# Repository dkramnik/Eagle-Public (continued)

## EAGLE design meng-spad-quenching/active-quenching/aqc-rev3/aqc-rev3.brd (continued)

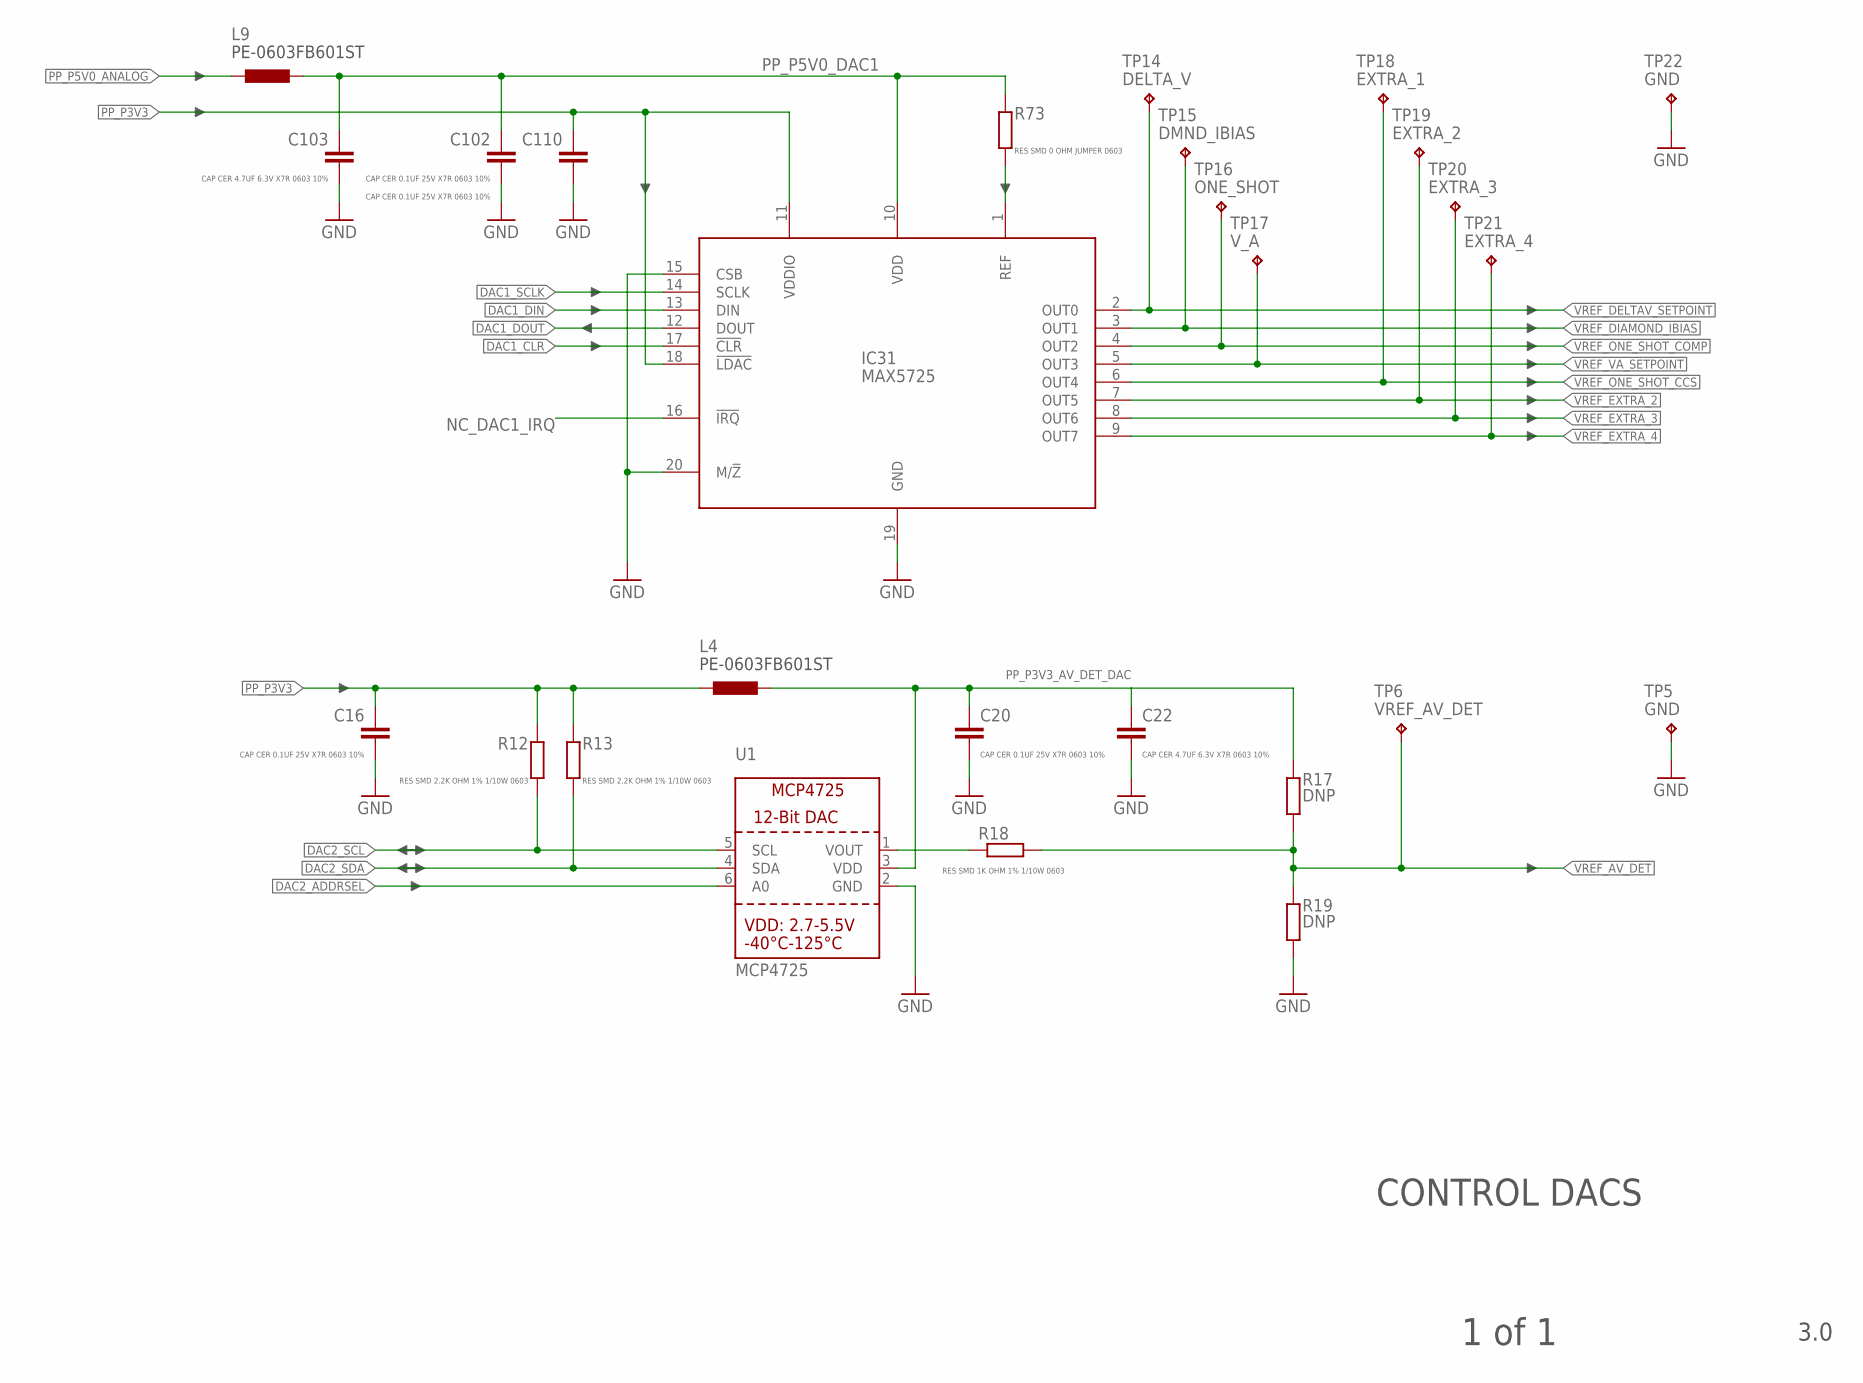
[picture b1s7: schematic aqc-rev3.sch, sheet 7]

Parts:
C16, C20, C102, C110: CAP CER 0.1UF 25V X7R 0603 10%; C0603
C22, C103: CAP CER 4.7UF 6.3V X7R 0603 10%; C0603
IC31: MAX5725; TSSOP20
L4, L9: PE-0603FB601ST; R0603
R12, R13: RES SMD 2.2K OHM 1% 1/10W 0603; R0603
R17, R19: DNP; R0603
R18: RES SMD 1K OHM 1% 1/10W 0603; R0603
R73: RES SMD 0 OHM JUMPER 0603; R0603
TP5, TP22: GND; KEYSTONE_5000_MINIATURE
TP6: VREF_AV_DET; KEYSTONE_5000_MINIATURE
TP14: DELTA_V; KEYSTONE_5000_MINIATURE
TP15: DMND_IBIAS; KEYSTONE_5000_MINIATURE
TP16: ONE_SHOT; KEYSTONE_5000_MINIATURE
TP17: V_A; KEYSTONE_5000_MINIATURE
TP18: EXTRA_1; KEYSTONE_5000_MINIATURE
TP19: EXTRA_2; KEYSTONE_5000_MINIATURE
TP20: EXTRA_3; KEYSTONE_5000_MINIATURE
TP21: EXTRA_4; KEYSTONE_5000_MINIATURE
U1: MCP4725; SOT23-6

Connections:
DAC1_!CLR: IC31.17 (!CLR); also elsewhere on the board
DAC1_DIN: IC31.13 (DIN); also elsewhere on the board
DAC1_DOUT: IC31.12 (DOUT); also elsewhere on the board
DAC1_SCLK: IC31.14 (SCLK); also elsewhere on the board
DAC2_ADDRSEL: U1.6 (A0); also elsewhere on the board
DAC2_SCL: R12.2, U1.5 (SCL); also elsewhere on the board
DAC2_SDA: R13.2, U1.4 (SDA); also elsewhere on the board
GND: C16.2, C20.2, C22.2, C102.2, C103.2, C110.2, IC31.15 (CSB), IC31.19 (GND), IC31.20 (M/!Z), R19.1, TP5.P$1, TP22.P$1, U1.2 (GND); also elsewhere on the board
unnamed: R18.2, U1.1 (VOUT)
unnamed: IC31.1 (REF), R73.2
NC_DAC1_IRQ: IC31.16 (!IRQ)
PP_P3V3: C16.1, C110.1, IC31.11 (VDDIO), IC31.18 (!LDAC), L4.1, R12.1, R13.1; also elsewhere on the board
PP_P3V3_AV_DET_DAC: C20.1, C22.1, L4.2, R17.2, U1.3 (VDD)
PP_P5V0_ANALOG: L9.1; also elsewhere on the board
PP_P5V0_DAC1: C102.1, C103.1, IC31.10 (VDD), L9.2, R73.1
VREF_AV_DET: R17.1, R18.1, R19.2, TP6.P$1; also elsewhere on the board
VREF_DELTAV_SETPOINT: IC31.2 (OUT0), TP14.P$1; also elsewhere on the board
VREF_DIAMOND_IBIAS: IC31.3 (OUT1), TP15.P$1; also elsewhere on the board
VREF_EXTRA_2: IC31.7 (OUT5), TP19.P$1
VREF_EXTRA_3: IC31.8 (OUT6), TP20.P$1
VREF_EXTRA_4: IC31.9 (OUT7), TP21.P$1
VREF_ONE_SHOT_CCS: IC31.6 (OUT4), TP18.P$1; also elsewhere on the board
VREF_ONE_SHOT_COMP: IC31.4 (OUT2), TP16.P$1; also elsewhere on the board
VREF_VA_SETPOINT: IC31.5 (OUT3), TP17.P$1; also elsewhere on the board

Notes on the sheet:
CONTROL DACS
3.0
1 of 1

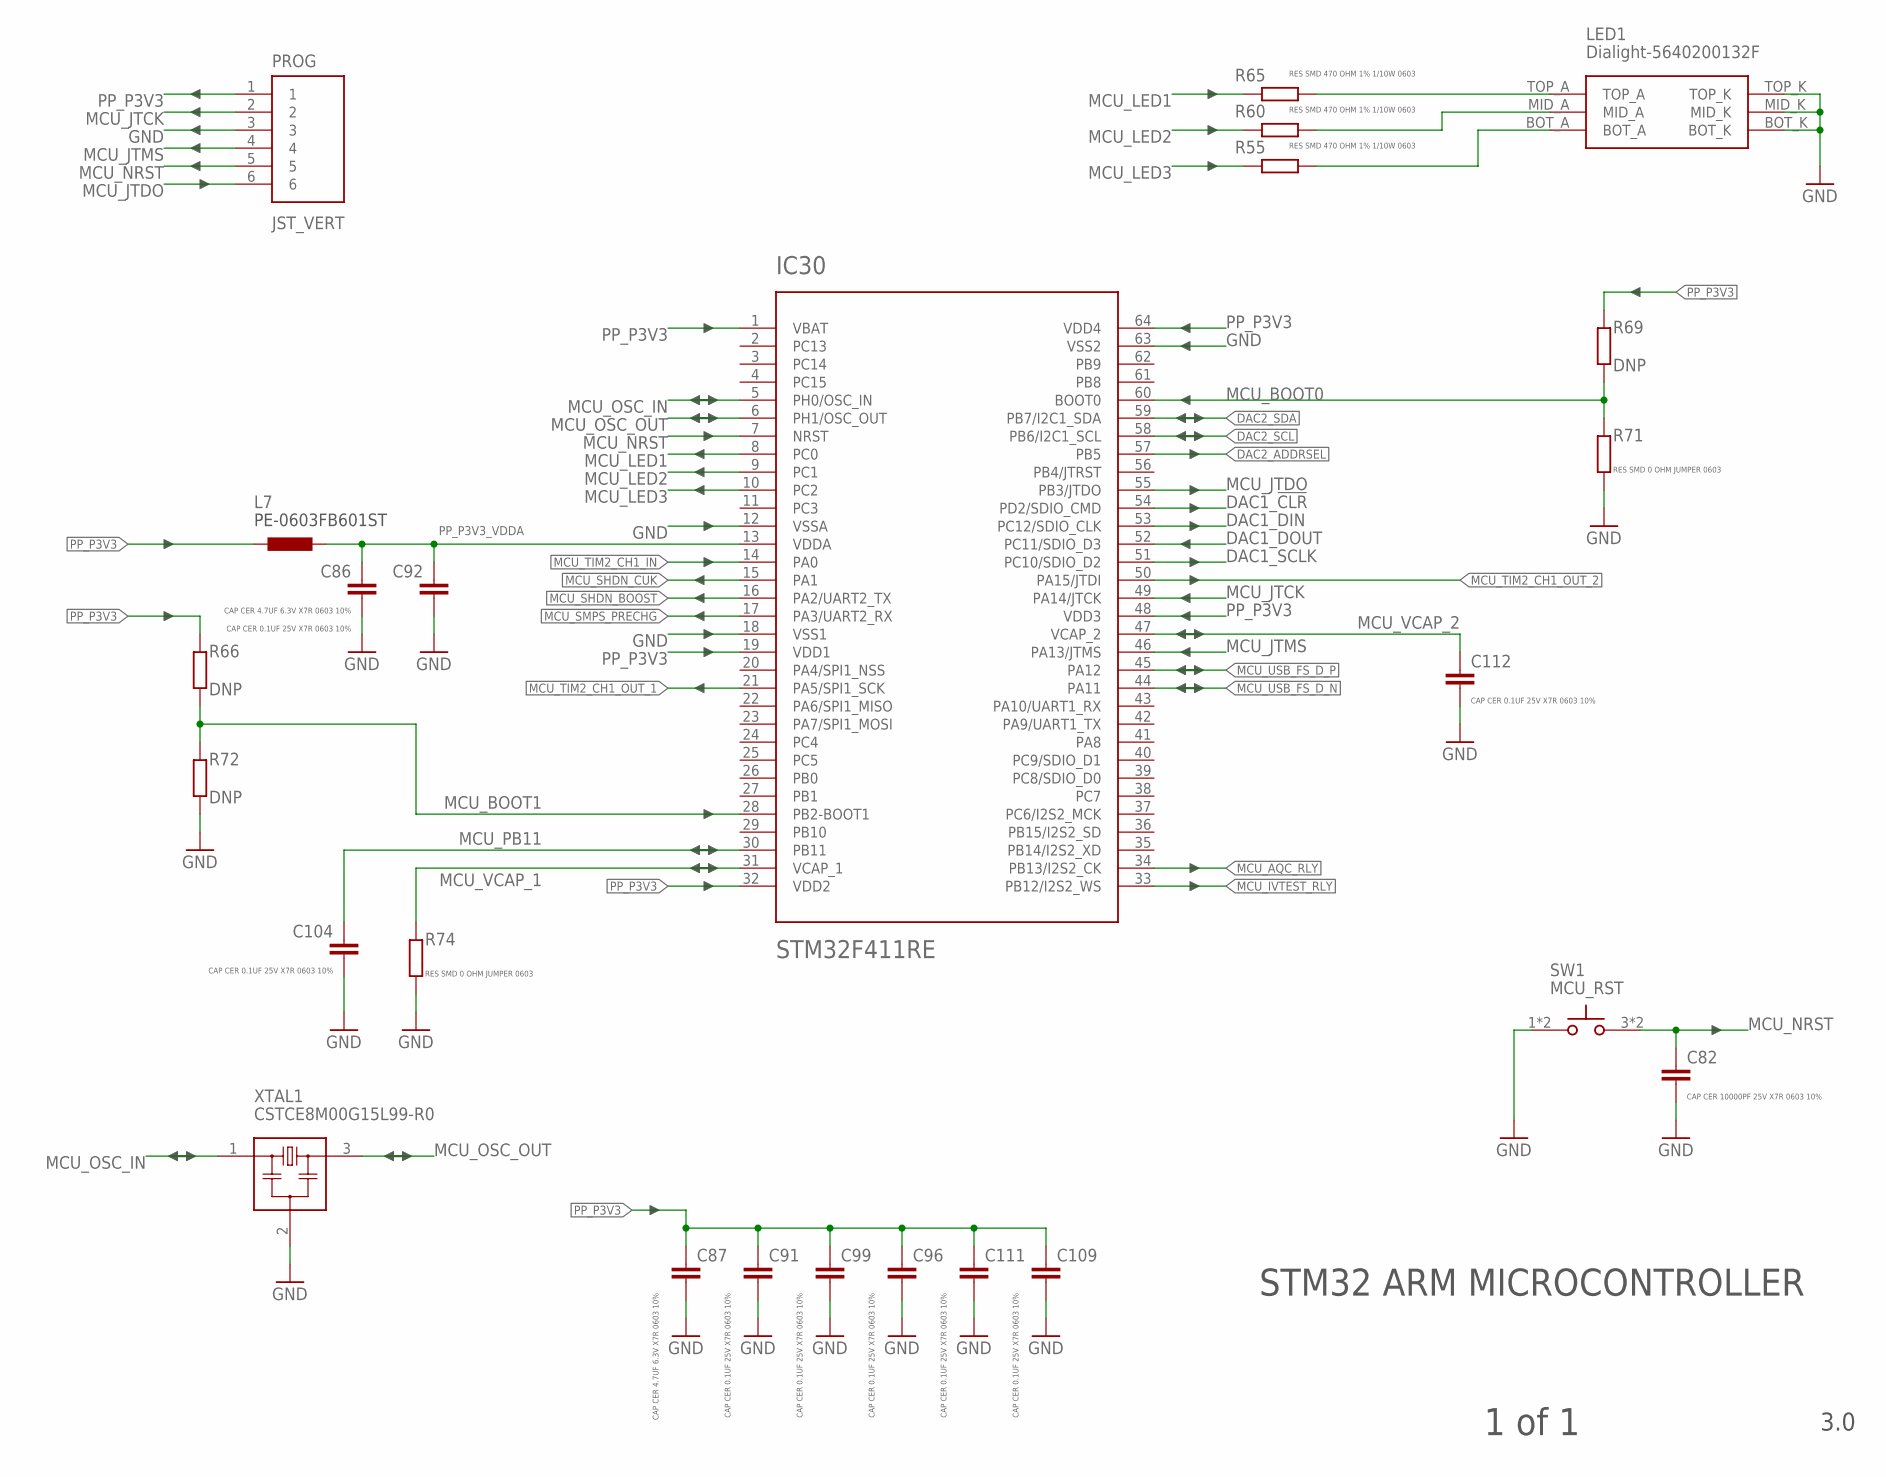
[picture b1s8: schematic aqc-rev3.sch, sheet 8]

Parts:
C82: CAP CER 10000PF 25V X7R 0603 10%; C0603
C86, C87: CAP CER 4.7UF 6.3V X7R 0603 10%; C0603
C91, C92, C96, C99, C104, C109, C111, C112: CAP CER 0.1UF 25V X7R 0603 10%; C0603
IC30: STM32F411RE; TQFP64_STM32
L7: PE-0603FB601ST; R0603
LED1: Dialight-5640200132F; CBI-564-0X00-XXX
PROG: JST_VERT; JST-6-SMD-VERT-1.0MM
R55, R60, R65: RES SMD 470 OHM 1% 1/10W 0603; R0603
R66, R69, R72: DNP; R0603
R71, R74: RES SMD 0 OHM JUMPER 0603; R0603
SW1: MCU_RST; E-SWITCH-TL3305AF160QG
XTAL1: CSTCE8M00G15L99-R0; CSTCE_G15L/CSTCE_GH5L

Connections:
!MCU_SHDN_BOOST: IC30.16 (PA2/UART2_TX); also elsewhere on the board
!MCU_SHDN_CUK: IC30.15 (PA1); also elsewhere on the board
!MCU_SMPS_PRECHG: IC30.17 (PA3/UART2_RX); also elsewhere on the board
DAC1_!CLR: IC30.54 (PD2/SDIO_CMD); also elsewhere on the board
DAC1_DIN: IC30.53 (PC12/SDIO_CLK); also elsewhere on the board
DAC1_DOUT: IC30.52 (PC11/SDIO_D3); also elsewhere on the board
DAC1_SCLK: IC30.51 (PC10/SDIO_D2); also elsewhere on the board
DAC2_ADDRSEL: IC30.57 (PB5); also elsewhere on the board
DAC2_SCL: IC30.58 (PB6/I2C1_SCL); also elsewhere on the board
DAC2_SDA: IC30.59 (PB7/I2C1_SDA); also elsewhere on the board
GND: C82.2, C86.2, C87.2, C91.2, C92.2, C96.2, C99.2, C104.2, C109.2, C111.2, C112.2, IC30.12 (VSSA), IC30.18 (VSS1), IC30.63 (VSS2), LED1.BOT_K, LED1.MID_K, LED1.TOP_K, PROG.3, R71.2, R72.2, R74.2, SW1.1, SW1.2, XTAL1.2 (GND); also elsewhere on the board
MCU_AQC_RLY: IC30.34 (PB13/I2S2_CK); also elsewhere on the board
MCU_BOOT0: IC30.60 (BOOT0), R69.2, R71.1
MCU_BOOT1: IC30.28 (PB2-BOOT1), R66.2, R72.1
MCU_IVTEST_RLY: IC30.33 (PB12/I2S2_WS); also elsewhere on the board
MCU_JTCK: IC30.49 (PA14/JTCK), PROG.2
MCU_JTDO: IC30.55 (PB3/JTDO), PROG.6
MCU_JTMS: IC30.46 (PA13/JTMS), PROG.4
MCU_LED1: IC30.8 (PC0), R65.2
MCU_LED2: IC30.9 (PC1), R60.2
MCU_LED3: IC30.10 (PC2), R55.2
MCU_NRST: C82.1, IC30.7 (NRST), PROG.5, SW1.3, SW1.4
MCU_OSC_IN: IC30.5 (PH0/OSC_IN), XTAL1.1 (LEFT)
MCU_OSC_OUT: IC30.6 (PH1/OSC_OUT), XTAL1.3 (RIGHT)
MCU_PB11: C104.1, IC30.30 (PB11)
MCU_TIM2_CH1_IN: IC30.14 (PA0); also elsewhere on the board
MCU_TIM2_CH1_OUT_1: IC30.21 (PA5/SPI1_SCK); also elsewhere on the board
MCU_TIM2_CH1_OUT_2: IC30.50 (PA15/JTDI); also elsewhere on the board
MCU_USB_FS_D_N: IC30.44 (PA11); also elsewhere on the board
MCU_USB_FS_D_P: IC30.45 (PA12); also elsewhere on the board
MCU_VCAP_1: IC30.31 (VCAP_1), R74.1
MCU_VCAP_2: C112.1, IC30.47 (VCAP_2)
unnamed: LED1.TOP_A, R65.1
unnamed: LED1.MID_A, R60.1
unnamed: LED1.BOT_A, R55.1
PP_P3V3: C87.1, C91.1, C96.1, C99.1, C109.1, C111.1, IC30.1 (VBAT), IC30.19 (VDD1), IC30.32 (VDD2), IC30.48 (VDD3), IC30.64 (VDD4), L7.1, PROG.1, R66.1, R69.1; also elsewhere on the board
PP_P3V3_VDDA: C86.1, C92.1, IC30.13 (VDDA), L7.2

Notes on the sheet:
STM32 ARM MICROCONTROLLER
3.0
1 of 1

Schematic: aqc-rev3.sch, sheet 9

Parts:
C26: CAP ALUM POLY 47UF 20% 20V SMD; CT7343
C79, C106, C107: CAP CER 0.1UF 25V X7R 0603 10%; C0603
C95: CAP CER 0.1UF 10V X7R 0402 10%; C0402
C97: CAP CER 10000PF 10V X7R 0402 10%; C0402
C98, C101: CAP CER 47PF 16V C0G 0402 5%; C0402
C105: CAP CER 10000PF 25V X7R 0603 10%; C0603
C108: CAP CER 4.7UF 6.3V X7R 0603 10%; C0603
H1, H2, H3, H4: MOUNT-PAD-ROUND3.2; 3,2-PAD
IC29: USBLC6-2SC6Y; SOT23-6L
IC32: LM1117; SOT-223
L8, L10: MI0805J102R-10; R0805
Q1: DMG2305UX-13; SOT23-WIDE
R58: RES SMD 4.7K OHM 1% 1/10W 0603; R0603
R62: RES SMD 100K OHM 1% 1/10W 0603; R0603
R67, R70: RES SMD 22 OHM 1% 1/10W 0402; R0402
TP23: TPTP15R; TP15R
X3, X6: KEYSTONE-7774
X8: 61729-0010BLF; PN61729-S

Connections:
!MCU_SMPS_PRECHG: R58.2; also elsewhere on the board
GND: C26.-, C95.2, C97.2, C98.2, C101.2, C105.2, C106.2, C107.2, C108.2, H1.B3,2, H2.B3,2, H3.B3,2, H4.B3,2, IC29.2 (GND), IC32.1 (GND), L10.2, X3.1, X3.2, X3.3, X3.4, X6.1, X6.2, X6.3, X6.4, X8.S1, X8.S2; also elsewhere on the board
MCU_USB_FS_D_N: C101.1, R70.1; also elsewhere on the board
MCU_USB_FS_D_P: C98.1, R67.1; also elsewhere on the board
unnamed: C79.1, Q1.1 (G), R58.1, R62.1
PP_P3V3: C95.1, C97.1, C106.1, IC29.5 (VBUS), IC32.2 (OUT), IC32.4 (TAB), TP23.TP; also elsewhere on the board
SMPS_USB_VDD: C26.+, C79.2, Q1.3 (D); also elsewhere on the board
USBCONN_P1: C105.1, L8.1, X8.1
USBCONN_P4: L10.1, X8.4
USBD_CONN_N: IC29.3 (I/O2), X8.2
USBD_CONN_P: IC29.1 (I/O1_1), X8.3
USBD_TVS_N: IC29.4 (I/O2_2), R70.2
USBD_TVS_P: IC29.6 (I/O1_2), R67.2
USB_VDD: C107.1, C108.1, IC32.3 (IN), L8.2, Q1.2 (S), R62.2

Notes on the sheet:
USB INPUT AND INRUSH LIMITING
3.0
1 of 1

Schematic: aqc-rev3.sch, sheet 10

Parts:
C3: CAP CER 1000PF 50V X7R 0603 10%; C0603
C4: CAP CER 1300PF 50V C0G 0603 5%; C0603
C13, C14, C25: CAP ALUM POLY 47UF 20% 20V SMD; CT7343
C15: CAP CER 4.7UF 25V X7R 0805 10%; C0805
C17: CAP CER 0.1UF 25V X7R 0603 10%; C0603
C18: CAP CER 0.015UF 50V X7R 0603 10%; C0603
C19: CAP CER 220PF 50V C0G 0603 5%; C0603
D1: CDBA140SL-HF; DO214AC
IC3: LT1534-1; SO16
L1: 25n; R0603
L2: Wurth-7447709471; WE_INDUCTOR_SIZE_CODE_1210
L3: SRF0703-820M; SRF0703
R3: RES SMD 0 OHM JUMPER 0603; R0603
R4, R9: DNP; R0603
R5: RES SMD 29.4K OHM 1% 1/10W 0603; R0603
R6: RES SMD 2.49K OHM 1% 1/10W 0603; R0603
R7: RES SMD 10 OHM 1% 1/10W 0603; R0603
R8: RES SMD 16.9K OHM 1% 1/10W 0603; R0603
R14, R15: RES SMD 1K OHM 1% 1/10W 0603; R0603
R16: RES SMD 6.8K OHM 1% 1/10W 0603; R0603
TP2, TP7: TPB1,27; B1,27

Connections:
!MCU_SHDN_BOOST: IC3.12 (!SHDN); also elsewhere on the board
BOOST_STAGE1: C13.+, C14.+, D1.C, L3.1, R4.1, R9.1
BOOST_SW_NODE: D1.A, IC3.2 (COL), L2.2, R7.1
GND: C3.1, C4.2, C13.-, C14.-, C15.2, C17.2, C18.2, C19.2, C25.-, IC3.1 (GND), IC3.8 (GND), IC3.9 (GND), IC3.16 (GND), L1.2, R6.2, R8.1, R14.2, R15.2; also elsewhere on the board
LBOOST_2: L3.2, L3.3
unnamed: IC3.7 (FB), R5.1, R6.1
unnamed: IC3.3 (PGND), L1.1
unnamed: C4.1, IC3.5 (CT)
unnamed: IC3.13 (RCSL), R15.1
unnamed: IC3.14 (RVSL), R14.1
unnamed: C3.2, R7.2
unnamed: C18.1, R16.1
unnamed: C19.1, IC3.11 (VC), R16.2
unnamed: IC3.6 (RT), R8.2
unnamed: R3.2, R4.2, R5.2
PP_P16V0_BOOST: C25.+, L3.4, R3.1, R9.2; also elsewhere on the board
SMPS_USB_VDD: C15.1, C17.1, IC3.15 (VIN), L2.1; also elsewhere on the board
TP_NFB_BOOST: IC3.10 (NFB), TP7.TP
TP_SYNC_BOOST: IC3.4 (SYNC), TP2.TP

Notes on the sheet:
POSITIVE DC/DC SMPS
3.0
1 of 1

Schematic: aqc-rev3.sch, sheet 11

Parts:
C27: CAP CER 10UF 10V X7R 1206 10%; C1206
C31: CAP CER 10000PF 25V X7R 0603 10%; C0603
C32: CAP CER 1300PF 50V C0G 0603 5%; C0603
C42: CAP ALUM POLY 68UF 20% 16V SMD; CT7343
C45, C57: CAP CER 4.7UF 25V X7R 0805 10%; C0805
C56: CAP CER 10UF 16V X7R 0805 20%; C0805
C67: CAP CER 0.1UF 25V X7R 0603 10%; C0603
C68: CAP CER 0.033UF 50V X7R 0603 10%; C0603
C69, C71: DNP; C0603
D2: CDBA140SL-HF; DO214AC
IC10: LT1534-1; SO16
L5: 25n; R0603
L6: SRF0703-820M; SRF0703
R29: RES SMD 100 OHM 1% 1/8W 0603; R0603
R30: RES SMD 16.9K OHM 1% 1/10W 0603; R0603
R41: RES SMD 1.4K OHM 1% 1/10W 0603; R0603
R43, R44, R48: RES SMD 1K OHM 1% 1/10W 0603; R0603
R45: RES SMD 2K OHM 1% 1/10W 0603; R0603
TP8, TP10: TPB1,27; B1,27

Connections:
!MCU_SHDN_CUK: IC10.12 (!SHDN); also elsewhere on the board
GND: C27.2, C31.2, C32.2, C45.2, C56.2, C57.2, C67.2, C68.2, C69.2, C71.2, D2.C, IC10.1 (GND), IC10.8 (GND), IC10.9 (GND), IC10.16 (GND), L5.2, R30.1, R43.2, R44.2, R48.2; also elsewhere on the board
unnamed: C32.1, IC10.5 (CT)
unnamed: IC10.3 (PGND), L5.1
unnamed: IC10.13 (RCSL), R44.1
unnamed: IC10.14 (RVSL), R43.1
unnamed: C31.1, R29.2
unnamed: C68.1, R45.1
unnamed: C69.1, IC10.11 (VC), R45.2
unnamed: IC10.6 (RT), R30.2
unnamed: IC10.10 (NFB), R41.2, R48.1
unnamed: C42.+, IC10.2 (COL), L6.3, R29.1
unnamed: C42.-, C71.1, D2.A, L6.4
PP_N6V0_CUK: C56.1, L6.2, R41.1; also elsewhere on the board
SMPS_USB_VDD: C27.1, C45.1, C57.1, C67.1, IC10.15 (VIN), L6.1; also elsewhere on the board
TP_FB_CUK: IC10.7 (FB), TP10.TP
TP_SYNC_CUK: IC10.4 (SYNC), TP8.TP

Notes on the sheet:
NEGATIVE DC/DC SMPS
3.0
1 of 1

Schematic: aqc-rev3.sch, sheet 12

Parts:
C1, C2, C5, C6, C41, C54: CAP CER 10000PF 25V X7R 0603 10%; C0603
C7, C8, C9, C10, C46, C53: CAP CER 0.1UF 25V X7R 0603 10%; C0603
C11: CAP CER 10UF 25V X5R 0805 10%; C0805
C12, C39: CAP CER 10UF 16V X7R 0805 20%; C0805
IC1, IC2: TPS7A4901; MSOP-8_POWER_PAD
IC9: TPS7A3001; MSOP-8_POWER_PAD
R1, R34: RES SMD 24K OHM 1% 1/10W 0603; R0603
R2: RES SMD 11.8K OHM 1% 1/10W 0603; R0603
R10, R32: RES SMD 76.8K OHM 1% 1/10W 0603; R0603
R11: RES SMD 137K OHM 1% 1/10W 0603; R0603
TP1, TP3, TP4, TP11: TPTP15R; TP15R

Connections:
GND: C1.2, C2.2, C7.2, C8.2, C9.2, C10.2, C11.2, C12.2, C39.2, C46.2, C53.2, C54.2, IC1.4 (GND), IC1.PAD (GND), IC2.4 (GND), IC2.PAD (GND), IC9.4 (GND), IC9.PAD (GND), R1.2, R2.2, R34.2, TP4.TP; also elsewhere on the board
LDO_N10V0_FB_CH1: C41.2, IC9.2 (FB), R32.1, R34.1
LDO_N10V0_NR_SS_CH1: C54.1, IC9.6 (NR/SS)
LDO_P5V0_FB_CH1: C5.2, IC1.2 (FB), R1.1, R10.1
LDO_P5V0_NR_SS_CH1: C1.1, IC1.6 (NR/SS)
LDO_P10V0_FB_CH1: C6.2, IC2.2 (FB), R2.1, R11.1
LDO_P10V0_NR_SS_CH1: C2.1, IC2.6 (NR/SS)
PP_N5V0_ANALOG: C39.1, C41.1, C46.1, IC9.1 (OUT), R32.2, TP11.TP; also elsewhere on the board
PP_N6V0_CUK: C53.1, IC9.5 (EN), IC9.8 (IN); also elsewhere on the board
PP_P5V0_ANALOG: C5.1, C9.1, C12.1, IC1.1 (OUT), R10.2, TP3.TP; also elsewhere on the board
PP_P15V0_ANALOG: C6.1, C7.1, C10.1, C11.1, IC1.5 (EN), IC1.8 (IN), IC2.1 (OUT), R11.2, TP1.TP; also elsewhere on the board
PP_P16V0_BOOST: C8.1, IC2.5 (EN), IC2.8 (IN); also elsewhere on the board

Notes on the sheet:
LINEAR POSTREGULATORS
3.0
1 of 1

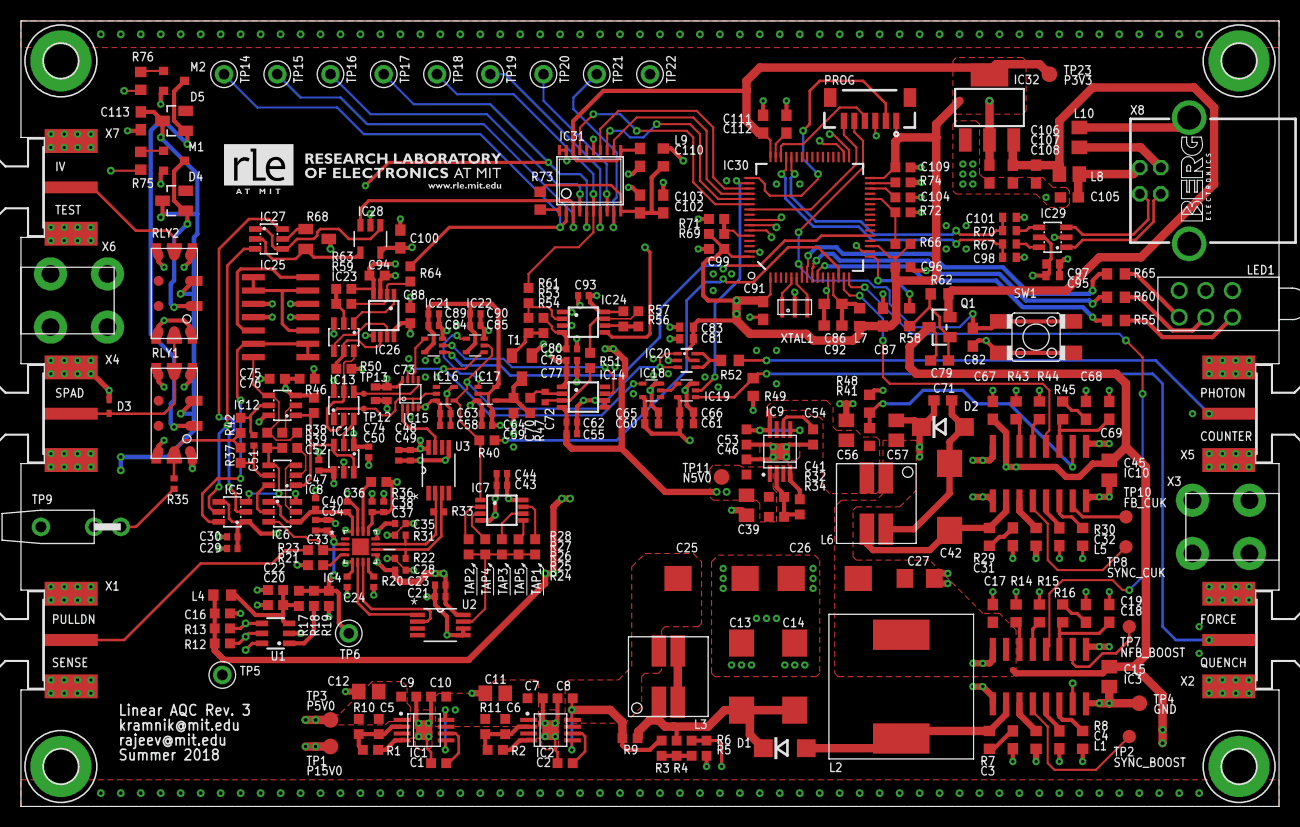
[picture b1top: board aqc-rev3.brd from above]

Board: 4 copper layers, 120.0 x 74.9 mm, 285 parts (0 on the bottom side), 166 nets.

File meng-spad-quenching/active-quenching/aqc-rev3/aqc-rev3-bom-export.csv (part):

"Qty";"Value";"Device";"Package";"Parts";"Description";"MF";"MPN";"OC_FARNELL";"OC_NEWARK";"PACKAGE";"PROD_ID";"SUPPLIER";"TP_SIGNAL_NAME";"VALUE";
"6";"0R";"R-EU_R0603";"R0603";"R3, R47, R51, R71, R73, R74";"RESISTOR, European symbol";"";"";"";"";"";"";"";"";"";
"1";"100R";"R-EU_R0402";"R0402";"R33";"RESISTOR, European symbol";"";"";"";"";"";"";"";"";"";
"3";"100R";"R-EU_R0603";"R0603";"R29, R75, R76";"RESISTOR, European symbol";"";"";"";"";"";"";"";"";"";
"2";"100R, 1%";"R-EU_R0603";"R0603";"R37, R42";"RESISTOR, European symbol";"";"";"";"";"";"";"";"";"";
"3";"100k";"R-EU_R0603";"R0603";"R56, R57, R62";"RESISTOR, European symbol";"";"";"";"";"";"";"";"";"";
"21";"100n";"C-EUC0402";"C0402";"C23, C29, C33, C35, C36, C37, C43, C49, C55, C58, C59, C61, C65, C73, C77, C80, C83, C89, C90, C93, C95";"CAPACITOR, European symbol";"";"";"";"";"";"";"";"";"";
"28";"100n";"C-EUC0603";"C0603";"C7, C8, C9, C10, C16, C17, C20, C46, C53, C67, C76, C79, C88, C91, C92, C94, C96, C99, C100, C102, C104, C106, C107, C109, C110, C111, C112, C113";"CAPACITOR, European symbol";"";"";"";"";"";"";"";"";"";
"1";"100p";"C-EUC0402";"C0402";"C51";"CAPACITOR, European symbol";"";"";"";"";"";"";"";"";"";
"1";"100p";"C-EUC0603";"C0603";"C70";"CAPACITOR, European symbol";"";"";"";"";"";"";"";"";"";
"1";"102k, 1%";"R-EU_R0603";"R0603";"R64";"RESISTOR, European symbol";"";"";"";"";"";"";"";"";"";
"1";"10R";"R-EU_R0603";"R0603";"R7";"RESISTOR, European symbol";"";"";"";"";"";"";"";"";"";
"2";"10k";"R-EU_R0603";"R0603";"R36, R54";"RESISTOR, European symbol";"";"";"";"";"";"";"";"";"";
"22";"10n";"C-EUC0402";"C0402";"C21, C24, C28, C30, C34, C38, C40, C44, C47, C48, C50, C60, C62, C63, C64, C66, C74, C78, C81, C84, C85, C97";"CAPACITOR, European symbol";"";"";"";"";"";"";"";"";"";
"11";"10n";"C-EUC0603";"C0603";"C1, C2, C5, C6, C31, C41, C52, C54, C75, C82, C105";"CAPACITOR, European symbol";"";"";"";"";"";"";"";"";"";
"3";"10u";"C-EUC0805";"C0805";"C11, C12, C39";"CAPACITOR, European symbol";"";"";"";"";"";"";"";"";"";
"1";"10u";"C-EUC1206";"C1206";"C27";"CAPACITOR, European symbol";"";"";"";"";"";"";"";"";"";
"1";"10u, 10V";"C-EUC0805";"C0805";"C56";"CAPACITOR, European symbol";"";"";"";"";"";"";"";"";"";
"1";"110R, 1%";"R-EU_R0603";"R0603";"R50";"RESISTOR, European symbol";"";"";"";"";"";"";"";"";"";
"1";"11k8";"R-EU_R0603";"R0603";"R2";"RESISTOR, European symbol";"";"";"";"";"";"";"";"";"";
"1";"127k, 1%";"R-EU_R0603";"R0603";"R59";"RESISTOR, European symbol";"";"";"";"";"";"";"";"";"";
"2";"1300p";"C-EUC0603";"C0603";"C4, C32";"CAPACITOR, European symbol";"";"";"";"";"";"";"";"";"";
"1";"137k";"R-EU_R0603";"R0603";"R11";"RESISTOR, European symbol";"";"";"";"";"";"";"";"";"";
"2";"150R";"R-EU_R0402";"R0402";"R22, R31";"RESISTOR, European symbol";"";"";"";"";"";"";"";"";"";
"1";"15n";"C-EUC0603";"C0603";"C18";"CAPACITOR, European symbol";"";"";"";"";"";"";"";"";"";
"2";"16k9";"R-EU_R0603";"R0603";"R8, R30";"RESISTOR, European symbol";"";"";"";"";"";"";"";"";"";
"6";"1k";"R-EU_R0603";"R0603";"R14, R15, R18, R43, R44, R48";"RESISTOR, European symbol";"";"";"";"";"";"";"";"";"";
"1";"1k4";"R-EU_R0603";"R0603";"R41";"RESISTOR, European symbol";"";"";"";"";"";"";"";"";"";
"1";"1n";"C-EUC0603";"C0603";"C3";"CAPACITOR, European symbol";"";"";"";"";"";"";"";"";"";
"2";"200R, 1%";"R-EU_R0603";"R0603";"R38, R39";"RESISTOR, European symbol";"";"";"";"";"";"";"";"";"";
"2";"220R, 1%";"R-EU_R0603";"R0603";"R23, R46";"RESISTOR, European symbol";"";"";"";"";"";"";"";"";"";
"2";"220k";"R-EU_R0603";"R0603";"R53, R61";"RESISTOR, European symbol";"";"";"";"";"";"";"";"";"";
"1";"220p";"C-EUC0603";"C0603";"C19";"CAPACITOR, European symbol";"";"";"";"";"";"";"";"";"";
"2";"22R";"R-EU_R0402";"R0402";"R67, R70";"RESISTOR, European symbol";"";"";"";"";"";"";"";"";"";
"2";"24k";"R-EU_R0603";"R0603";"R1, R34";"RESISTOR, European symbol";"";"";"";"";"";"";"";"";"";
"2";"25n";"INDUCTOR0603";"R0603";"L1, L5";"";"";"";"";"";"";"";"";"";"";
"1";"274R, 1%";"R-EU_R0603";"R0603";"R63";"RESISTOR, European symbol";"";"";"";"";"";"";"";"";"";
"1";"29k4";"R-EU_R0603";"R0603";"R5";"RESISTOR, European symbol";"";"";"";"";"";"";"";"";"";
"1";"2k";"R-EU_R0603";"R0603";"R45";"RESISTOR, European symbol";"";"";"";"";"";"";"";"";"";
"2";"2k2";"R-EU_R0603";"R0603";"R12, R13";"RESISTOR, European symbol";"";"";"";"";"";"";"";"";"";
"1";"2k49";"R-EU_R0603";"R0603";"R6";"RESISTOR, European symbol";"";"";"";"";"";"";"";"";"";
"1";"33n";"C-EUC0603";"C0603";"C68";"CAPACITOR, European symbol";"";"";"";"";"";"";"";"";"";
"3";"470R";"R-EU_R0603";"R0603";"R55, R60, R65";"RESISTOR, European symbol";"";"";"";"";"";"";"";"";"";
"2";"47p";"C-EUC0402";"C0402";"C98, C101";"CAPACITOR, European symbol";"";"";"";"";"";"";"";"";"";
"4";"47u, 20V";"CPOL-EUCT7343";"CT7343";"C13, C14, C25, C26";"POLARIZED CAPACITOR, European symbol";"";"";"";"";"";"";"";"";"";
"2";"49R9";"R-EU_R0402";"R0402";"R20, R35";"RESISTOR, European symbol";"";"";"";"";"";"";"";"";"";
"3";"49R9";"R-EU_R0603";"R0603";"R40, R49, R52";"RESISTOR, European symbol";"";"";"";"";"";"";"";"";"";
"1";"4k7";"R-EU_R0603";"R0603";"R58";"RESISTOR, European symbol";"";"";"";"";"";"";"";"";"";
"5";"4u7";"C-EUC0603";"C0603";"C22, C86, C87, C103, C108";"CAPACITOR, European symbol";"";"";"";"";"";"";"";"";"";
"3";"4u7";"C-EUC0805";"C0805";"C15, C45, C57";"CAPACITOR, European symbol";"";"";"";"";"";"";"";"";"";
"1";"5640200132F";"CBI-564-0X00-XXX-3LED";"CBI-564-0X00-XXX";"LED1";"";"";"";"";"";"";"";"";"";"564-0x00-xxx";
"1";"68u, 16V";"CPOL-EUCT7343";"CT7343";"C42";"POLARIZED CAPACITOR, European symbol";"";"";"";"";"";"";"";"";"";
"1";"6k8";"R-EU_R0603";"R0603";"R16";"RESISTOR, European symbol";"";"";"";"";"";"";"";"";"";
"1";"732-1699-2-ND";"WE_INDUCTOR";"WE_INDUCTOR_SIZE_CODE_1210";"L2";"";"";"";"";"";"";"";"";"";"";
"1";"74AHC1G04DCK";"74AHC1G04DCK";"SC70-5";"IC18";"INVERTER Gate";"";"";"";"";"";"";"";"";"";
"2";"74AHC1G08DCK";"74AHC1G08DCK";"SC70-5";"IC21, IC22";"2-input AND gate";"";"";"";"";"";"";"";"";"";
"1";"74AHC1G14DCK";"74AHC1G14DCK";"SC70-5";"IC16";"Single Schmitt-Trigger Inverter Gate";"";"";"";"";"";"";"";"";"";
"1";"74AHC1G32DCK";"74AHC1G32DCK";"SC70-5";"IC19";"2-input OR gate";"";"";"";"";"";"";"";"";"";
"2";"76k8";"R-EU_R0603";"R0603";"R10, R32";"RESISTOR, European symbol";"";"";"";"";"";"";"";"";"";
"1";"ADCMP582";"ADCMP582";"QFN50P300X300X80-16N";"IC4";"Ultrafast SiGe Voltage Comparator w/. PECL Outputs";"";"";"";"";"";"";"";"";"";
"2";"BAS40";"BAS40";"SOT23";"D4, D5";"Silicon Schottky Diodes";"";"";"";"";"";"";"";"";"";
"2";"BSS806N";"BSS806N";"SOT23R_INFINEON";"M1, M2";"";"";"";"";"";"";"";"";"";"";
"2";"CDBA140SL-HF";"DIODE-DO214AC";"DO214AC";"D1, D2";"DIODE";"";"";"";"";"";"";"";"";"";
"1";"CONN_FORCE_QUENCH";"SMA-142-0701-881/886";"J502-ND-142-0701-881/886";"X2";"SMA 50 Ohm End Launch Jack Receptacle - Round Contact";"JOHNSON COMPONENTS";"142-0711-871";"unknown";"01C1639";"";"";"";"";"";
"1";"CONN_PHOTON_COUNTER";"SMA-142-0701-881/886";"J502-ND-142-0701-881/886";"X5";"SMA 50 Ohm End Launch Jack Receptacle - Round Contact";"JOHNSON COMPONENTS";"142-0701-881";"1608603";"08B906";"";"";"";"";"";
"1";"CONN_PULLDN_SENSE";"SMA-142-0701-881/886";"J502-ND-142-0701-881/886";"X1";"SMA 50 Ohm End Launch Jack Receptacle - Round Contact";"JOHNSON COMPONENTS";"142-0711-871";"unknown";"01C1639";"";"";"";"";"";
"1";"CONN_SMU";"SMA-142-0701-881/886";"J502-ND-142-0701-881/886";"X7";"SMA 50 Ohm End Launch Jack Receptacle - Round Contact";"JOHNSON COMPONENTS";"142-0701-881";"1608603";"08B906";"";"";"";"";"";
"1";"CONN_SPAD";"SMA-142-0701-881/886";"J502-ND-142-0701-881/886";"X4";"SMA 50 Ohm End Launch Jack Receptacle - Round Contact";"JOHNSON COMPONENTS";"142-0701-881";"1608603";"08B906";"";"";"";"";"";
"2";"CRF05-1A";"MEDER_CRF05-1A";"MEDER_RELAY_CRF";"RLY1, RLY2";"MEDER CRF05-1A RF Reed Relay in a ceramic surface mount package.";"";"";"";"";"";"";"";"";"CRF05-1A";
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
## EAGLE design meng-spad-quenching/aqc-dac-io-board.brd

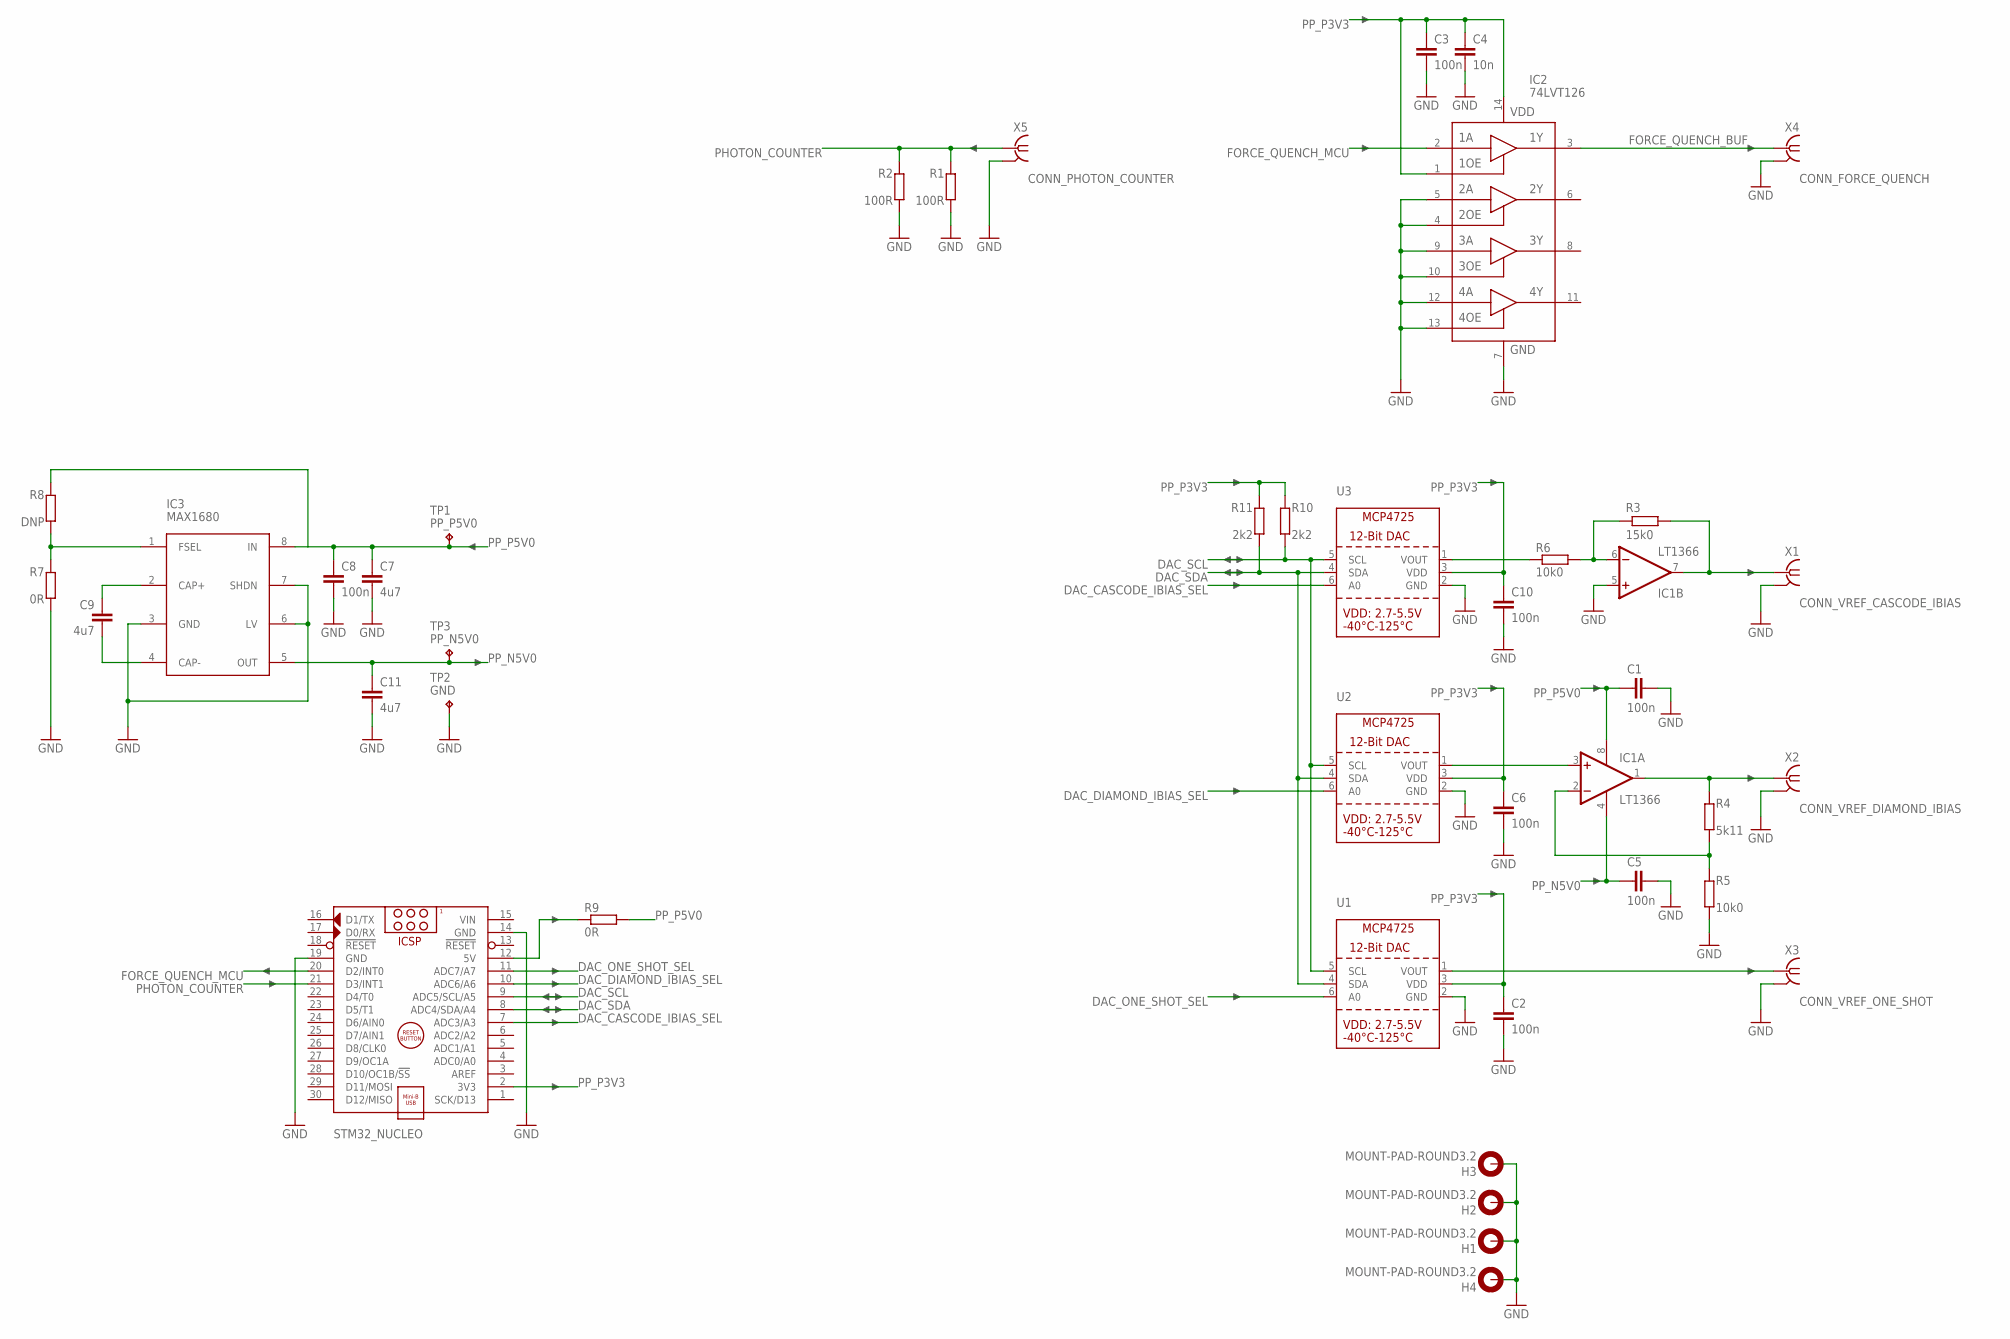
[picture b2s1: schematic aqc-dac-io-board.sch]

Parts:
C1, C2, C3, C5, C6, C8, C10: 100n; C0603
C4: 10n; C0603
C7, C9, C11: 4u7; C0805
H1, H2, H3, H4: MOUNT-PAD-ROUND3.2; 3,2-PAD
IC1: LT1366; SO08
IC2: 74LVT126; SO14
IC3: MAX1680; SO8
R1, R2: 100R; R0603
R3: 15k0; R0603
R4: 5k11; R0603
R5, R6: 10k0; R0603
R7, R9: 0R; R0603
R8: DNP; R0603
R10, R11: 2k2; R0603
STM32_NUCLEO: ARDUINO_NANO
TP1: PP_P5V0; KEYSTONE_5000_MINIATURE
TP2: GND; KEYSTONE_5000_MINIATURE
TP3: PP_N5V0; KEYSTONE_5000_MINIATURE
U1, U2, U3: DAC_MCP4725; SOT23-6
X1: CONN_VREF_CASCODE_IBIAS; J502-ND-142-0701-801/806
X2: CONN_VREF_DIAMOND_IBIAS; J502-ND-142-0701-801/806
X3: CONN_VREF_ONE_SHOT; J502-ND-142-0701-801/806
X4: CONN_FORCE_QUENCH; J502-ND-142-0701-801/806
X5: CONN_PHOTON_COUNTER; J502-ND-142-0701-801/806

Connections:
DAC_CASCODE_IBIAS_SEL: STM32_NUCLEO.7 (ADC3/A3), U3.6 (A0)
DAC_DIAMOND_IBIAS_SEL: STM32_NUCLEO.10 (ADC6/A6), U2.6 (A0)
DAC_ONE_SHOT_SEL: STM32_NUCLEO.11 (ADC7/A7), U1.6 (A0)
DAC_SCL: R10.1, STM32_NUCLEO.9 (ADC5/SCL/A5), U1.5 (SCL), U2.5 (SCL), U3.5 (SCL)
DAC_SDA: R11.1, STM32_NUCLEO.8 (ADC4/SDA/A4), U1.4 (SDA), U2.4 (SDA), U3.4 (SDA)
FORCE_QUENCH_BUF: IC2.3 (1Y), X4.1
FORCE_QUENCH_MCU: IC2.2 (1A), STM32_NUCLEO.20 (D2/INT0)
GND: C1.2, C2.2, C3.2, C4.2, C5.2, C6.2, C7.2, C8.2, C10.2, C11.2, H1.B3,2, H2.B3,2, H3.B3,2, H4.B3,2, IC1.5 (+IN), IC2.4 (2OE), IC2.5 (2A), IC2.7 (GND), IC2.9 (3A), IC2.10 (3OE), IC2.12 (4A), IC2.13 (4OE), IC3.3 (GND), IC3.6 (LV), IC3.7 (SHDN), R1.1, R2.1, R5.1, R7.1, STM32_NUCLEO.14 (GND), STM32_NUCLEO.19 (GND), TP2.P$1, U1.2 (GND), U2.2 (GND), U3.2 (GND), X1.G@1 (GND), X1.G@2 (GND), X1.G@3 (GND), X1.G@4 (GND), X2.G@1 (GND), X2.G@2 (GND), X2.G@3 (GND), X2.G@4 (GND), X3.G@1 (GND), X3.G@2 (GND), X3.G@3 (GND), X3.G@4 (GND), X4.G@1 (GND), X4.G@2 (GND), X4.G@3 (GND), X4.G@4 (GND), X5.G@1 (GND), X5.G@2 (GND), X5.G@3 (GND), X5.G@4 (GND)
unnamed: U1.1 (VOUT), X3.1
unnamed: R6.2, U3.1 (VOUT)
unnamed: IC1.6 (-IN), R3.2, R6.1
unnamed: IC3.1 (FSEL), R7.2, R8.1
unnamed: IC1.7 (OUT), R3.1, X1.1
unnamed: IC1.3 (+IN), U2.1 (VOUT)
unnamed: IC1.1 (OUT), R4.2, X2.1
unnamed: IC1.2 (-IN), R4.1, R5.2
unnamed: R9.2, STM32_NUCLEO.12 (5V)
unnamed: C9.2, IC3.4 (CAP-)
unnamed: C9.1, IC3.2 (CAP+)
PHOTON_COUNTER: R1.2, R2.2, STM32_NUCLEO.21 (D3/INT1), X5.1
PP_N5V0: C5.1, C11.1, IC1.4 (V-), IC3.5 (OUT), TP3.P$1
PP_P3V3: C2.1, C3.1, C4.1, C6.1, C10.1, IC2.1 (1OE), IC2.14 (VDD), R10.2, R11.2, STM32_NUCLEO.2 (3V3), U1.3 (VDD), U2.3 (VDD), U3.3 (VDD)
PP_P5V0: C1.1, C7.1, C8.1, IC1.8 (V+), IC3.8 (IN), R8.2, R9.1, TP1.P$1
VIN: STM32_NUCLEO.15 (VIN)
